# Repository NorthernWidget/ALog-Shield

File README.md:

# ALog-Shield
An Arduino shield with all the capabilities of the ALog BottleLogger

## Citation

If you use this data logger in a publication, please cite:

**Wickert, A. D., C. T. Sandell, B. Schulz, and G.-H. C. Ng (2019), [Open-source Arduino-compatible data loggers designed for field research](https://doi.org/10.5194/hess-23-2065-2019), *Hydrol. Earth Syst. Sci.*, *23*, 2065–2076, doi:10.5194/hess-23-2065-2019.**

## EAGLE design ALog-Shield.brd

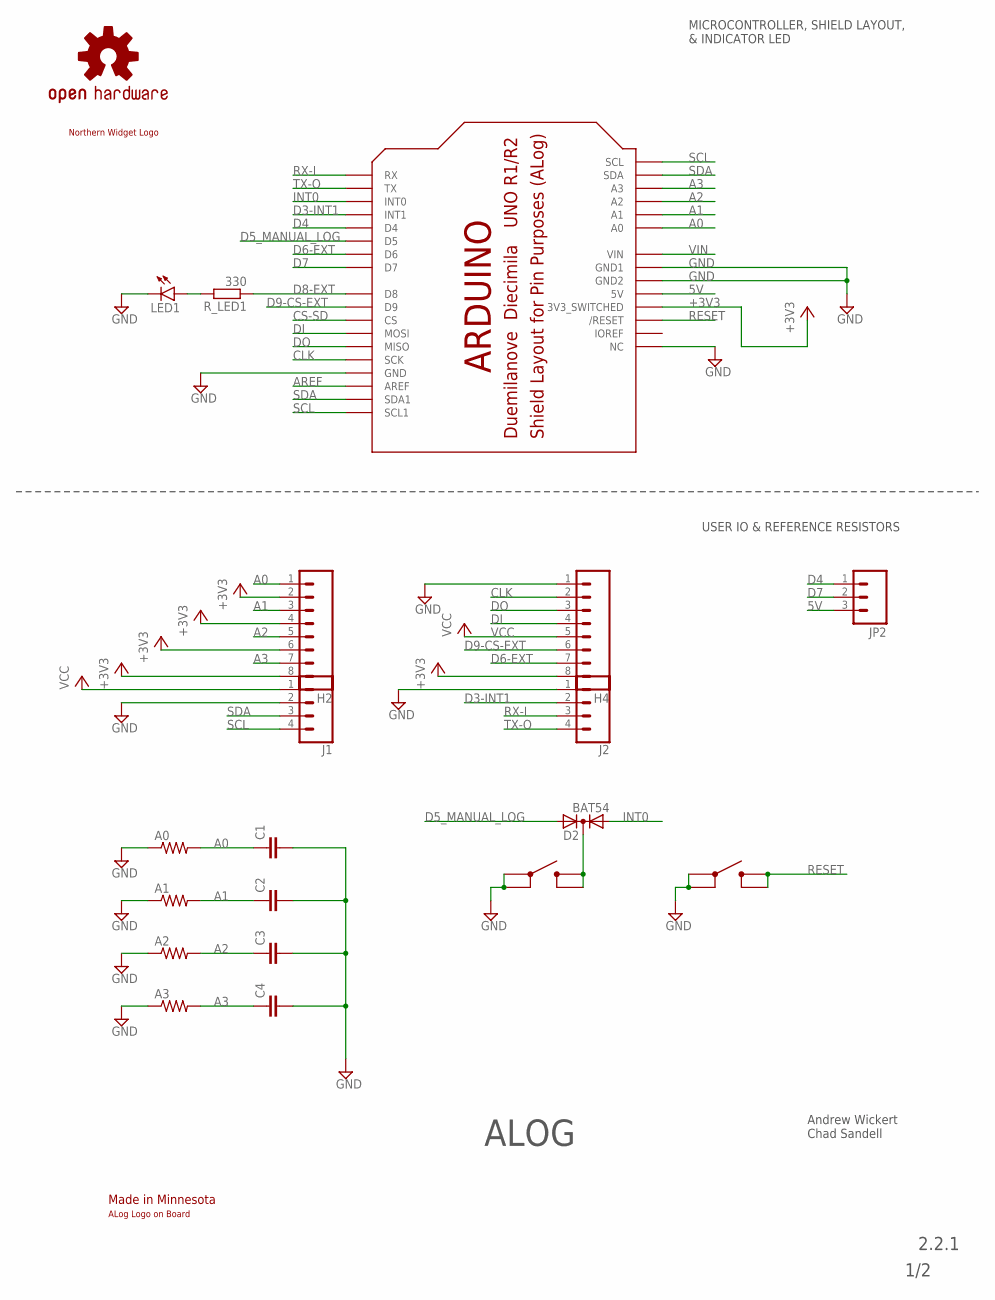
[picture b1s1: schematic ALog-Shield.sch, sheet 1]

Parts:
A0, A1, A2, A3: R-US_0207/10; 0207/10
C1, C2, C3, C4: C-EU0.1UFC0603; C0603
D2: BAT54; SOT23C
H2, H4: M083.5MM-8; SCREWTERMINAL-3.5MM-8
J1, J2: CONN_04SCREW; SCREWTERMINAL-3.5MM-4
JP2: M03SCREW; SCREWTERMINAL-3.5MM-3
LED1: LED1206; LED-1206
LOG: LOG; SWITCH_4.2X3.2
LOGO1: OSHW-LOGOL; OSHW-LOGO-L
RESET: Reset; SWITCH_4.2X3.2
R_LED1: 330; R0603
U$1: NWLOGO_MED
U$2: MADE_IN_MN_220_SHIELD; MADE_IN_MN_SHIELD_220
U$3: ALOG_LOG
U$9: AWICKERT_ARDUINO_SHIELD_PIN_PURPOSE; AWICKERT_ARDUINO_SHIELD_PINS_ONLY

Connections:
5V: JP2.3, U$9.5V
+3V3: H2.2, H2.4, H2.6, H2.8, H4.8, U$9.3.3V (3V3_SWITCHED); also elsewhere on the board
A0: A0.2, C1.1, H2.1, U$9.A0
A1: A1.2, C2.1, H2.3, U$9.A1
A2: A2.2, C3.1, H2.5, U$9.A2
A3: A3.2, C4.1, H2.7, U$9.A3
AREF: U$9.AREF; also elsewhere on the board
CLK: H4.2, U$9.D13 (SCK); also elsewhere on the board
CS-SD: U$9.D10 (CS); also elsewhere on the board
D3-INT1: J2.2, U$9.D3 (INT1)
D4: JP2.1, U$9.D4
D5_MANUAL_LOG: D2.2 (A2), U$9.D5
D6-EXT: H4.7, U$9.D6
D7: JP2.2, U$9.D7
D8-EXT: R_LED1.1, U$9.D8
D9-CS-EXT: H4.6, U$9.D9
DI: H4.4, U$9.D11 (MOSI); also elsewhere on the board
DO: H4.3, U$9.D12 (MISO); also elsewhere on the board
GND: A0.1, A1.1, A2.1, A3.1, C1.2, C2.2, C3.2, C4.2, H4.1, J1.2, J2.1, LED1.C, LOG.1, LOG.2, RESET.1, RESET.2, U$9.GND@0 (GND), U$9.GND@1 (GND1), U$9.GND@2 (GND2), U$9.NC; also elsewhere on the board
INT0: D2.1 (A1), U$9.D2 (INT0); also elsewhere on the board
LED+1: LED1.A, R_LED1.2
unnamed: D2.3 (K), LOG.3 (4), LOG.4 (3)
RESET: RESET.3 (4), RESET.4 (3), U$9.RES (/RESET)
RX-I: J2.3, U$9.RX
SCL: J1.4, U$9.A5 (SCL), U$9.SCL (SCL1); also elsewhere on the board
SDA: J1.3, U$9.A4 (SDA), U$9.SDA (SDA1); also elsewhere on the board
TX-O: J2.4, U$9.TX
VCC: H4.5, J1.1; also elsewhere on the board
VIN: U$9.VIN

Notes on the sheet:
MICROCONTROLLER, SHIELD LAYOUT, & INDICATOR LED
USER IO & REFERENCE RESISTORS
2.2.1
1/2
Andrew Wickert Chad Sandell
ALOG

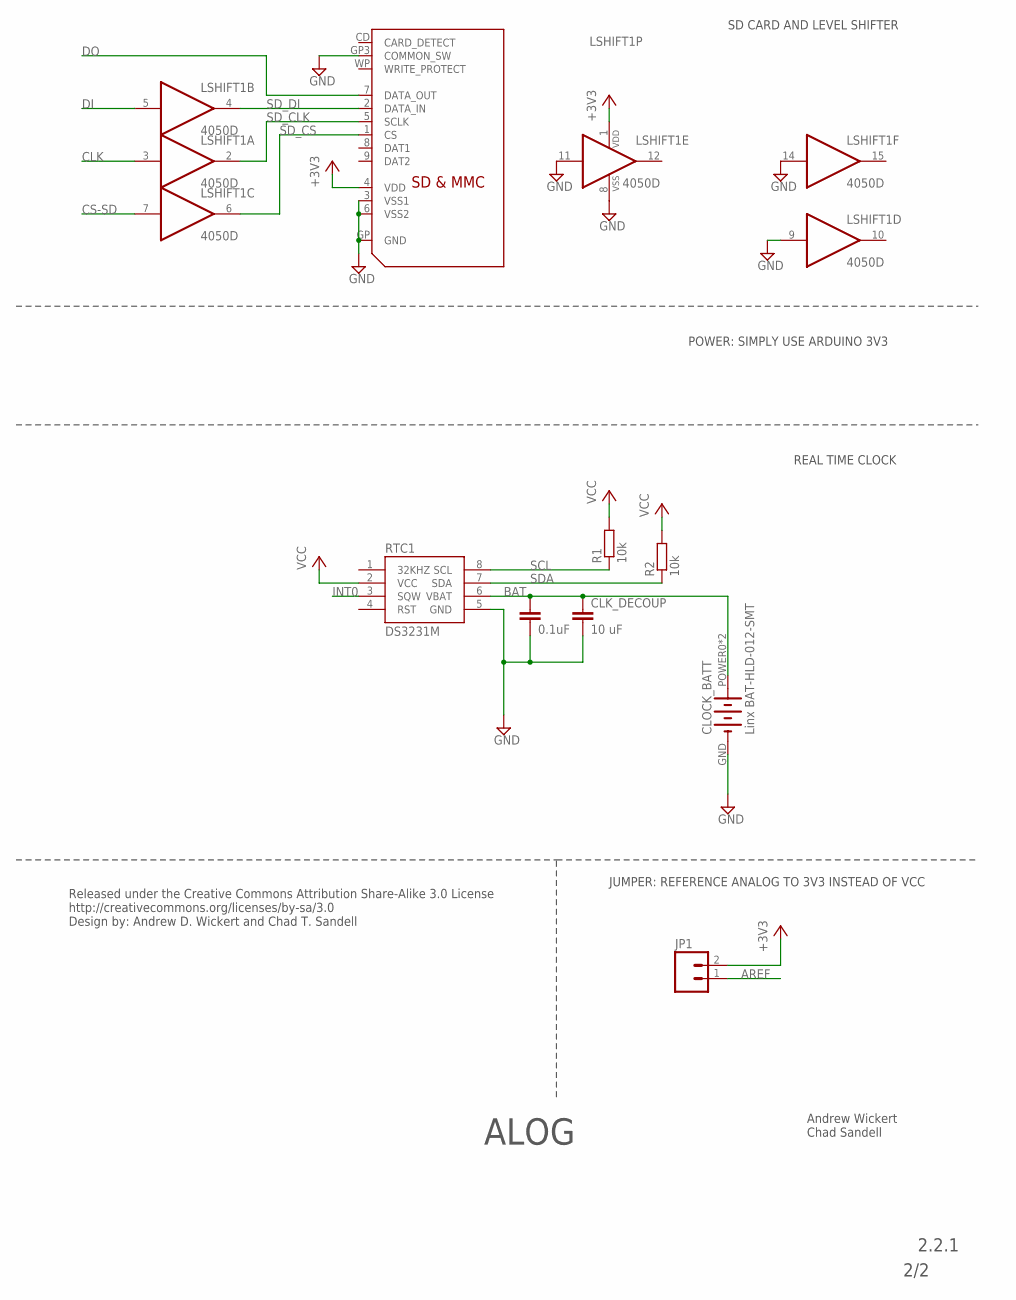
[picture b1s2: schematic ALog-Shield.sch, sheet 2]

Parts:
CLK_DECOUP: 10 uF; C0805
CLOCK_BATT: Linx BAT-HLD-012-SMT; LINX_BAT-HLD-012-SMT
CLOCK_BATT_DECOUP: 0.1uF; C0603
JP1: M02LOCK; 1X02_LOCK
LSHIFT1: 4050D; SO16
R1, R2: 10k; R0603
RTC1: DS3231M; SO08
SD1: SDMMC06132; 06132

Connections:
+3V3: JP1.2, LSHIFT1.1 (VDD), SD1.4 (VDD); also elsewhere on the board
AREF: JP1.1; also elsewhere on the board
BAT: CLK_DECOUP.1, CLOCK_BATT.POWER0 (+), CLOCK_BATT.POWER1 (+), CLOCK_BATT_DECOUP.1, RTC1.6 (VBAT)
CLK: LSHIFT1.3 (I); also elsewhere on the board
CS-SD: LSHIFT1.7 (I); also elsewhere on the board
DI: LSHIFT1.5 (I); also elsewhere on the board
DO: SD1.7 (DATA_OUT); also elsewhere on the board
GND: CLK_DECOUP.2, CLOCK_BATT.GND (-), CLOCK_BATT_DECOUP.2, LSHIFT1.8 (VSS), LSHIFT1.9 (I), LSHIFT1.11 (I), LSHIFT1.14 (I), RTC1.5 (GND), SD1.3 (VSS1), SD1.6 (VSS2), SD1.GP (GND), SD1.GP3 (COMMON_SW); also elsewhere on the board
INT0: RTC1.3 (SQW); also elsewhere on the board
SCL: R1.1, RTC1.8 (SCL); also elsewhere on the board
SDA: R2.1, RTC1.7 (SDA); also elsewhere on the board
SD_CLK: LSHIFT1.2 (O), SD1.5 (SCLK)
SD_CS: LSHIFT1.6 (O), SD1.1 (CS)
SD_DI: LSHIFT1.4 (O), SD1.2 (DATA_IN)
VCC: R1.2, R2.2, RTC1.2 (VCC); also elsewhere on the board

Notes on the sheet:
REAL TIME CLOCK
SD CARD AND LEVEL SHIFTER
POWER: SIMPLY USE ARDUINO 3V3
2.2.1
ALOG
2/2
Andrew Wickert Chad Sandell
Released under the Creative Commons Attribution Share-Alike 3.0 License http://creativecommons.org/licenses/by-sa/3.0 Design by: Andrew D. Wickert and Chad T. Sandell
JUMPER: REFERENCE ANALOG TO 3V3 INSTEAD OF VCC

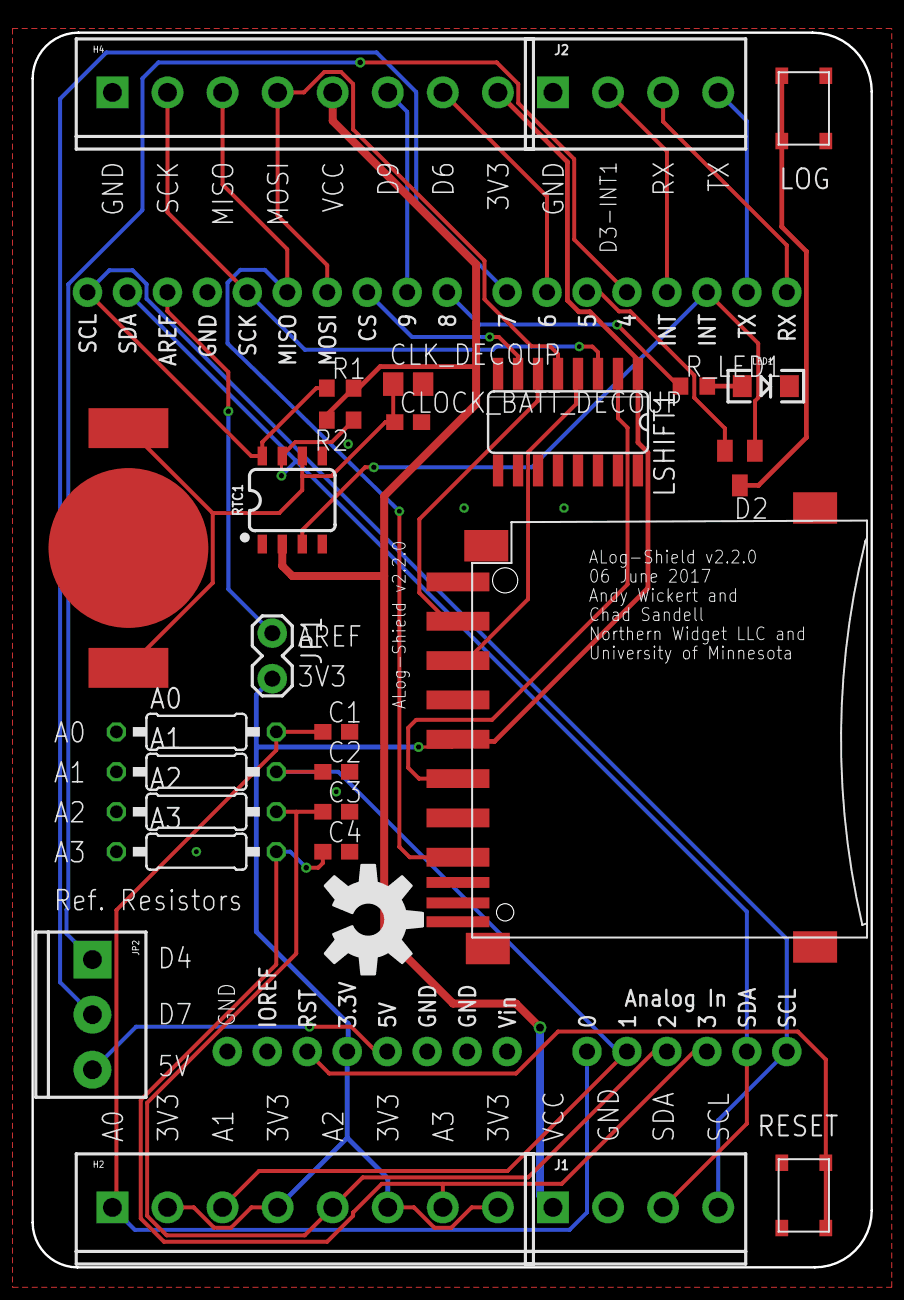
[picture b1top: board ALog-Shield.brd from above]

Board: 2 copper layers, 53.3 x 78.5 mm, 32 parts (1 on the bottom side), 32 nets.

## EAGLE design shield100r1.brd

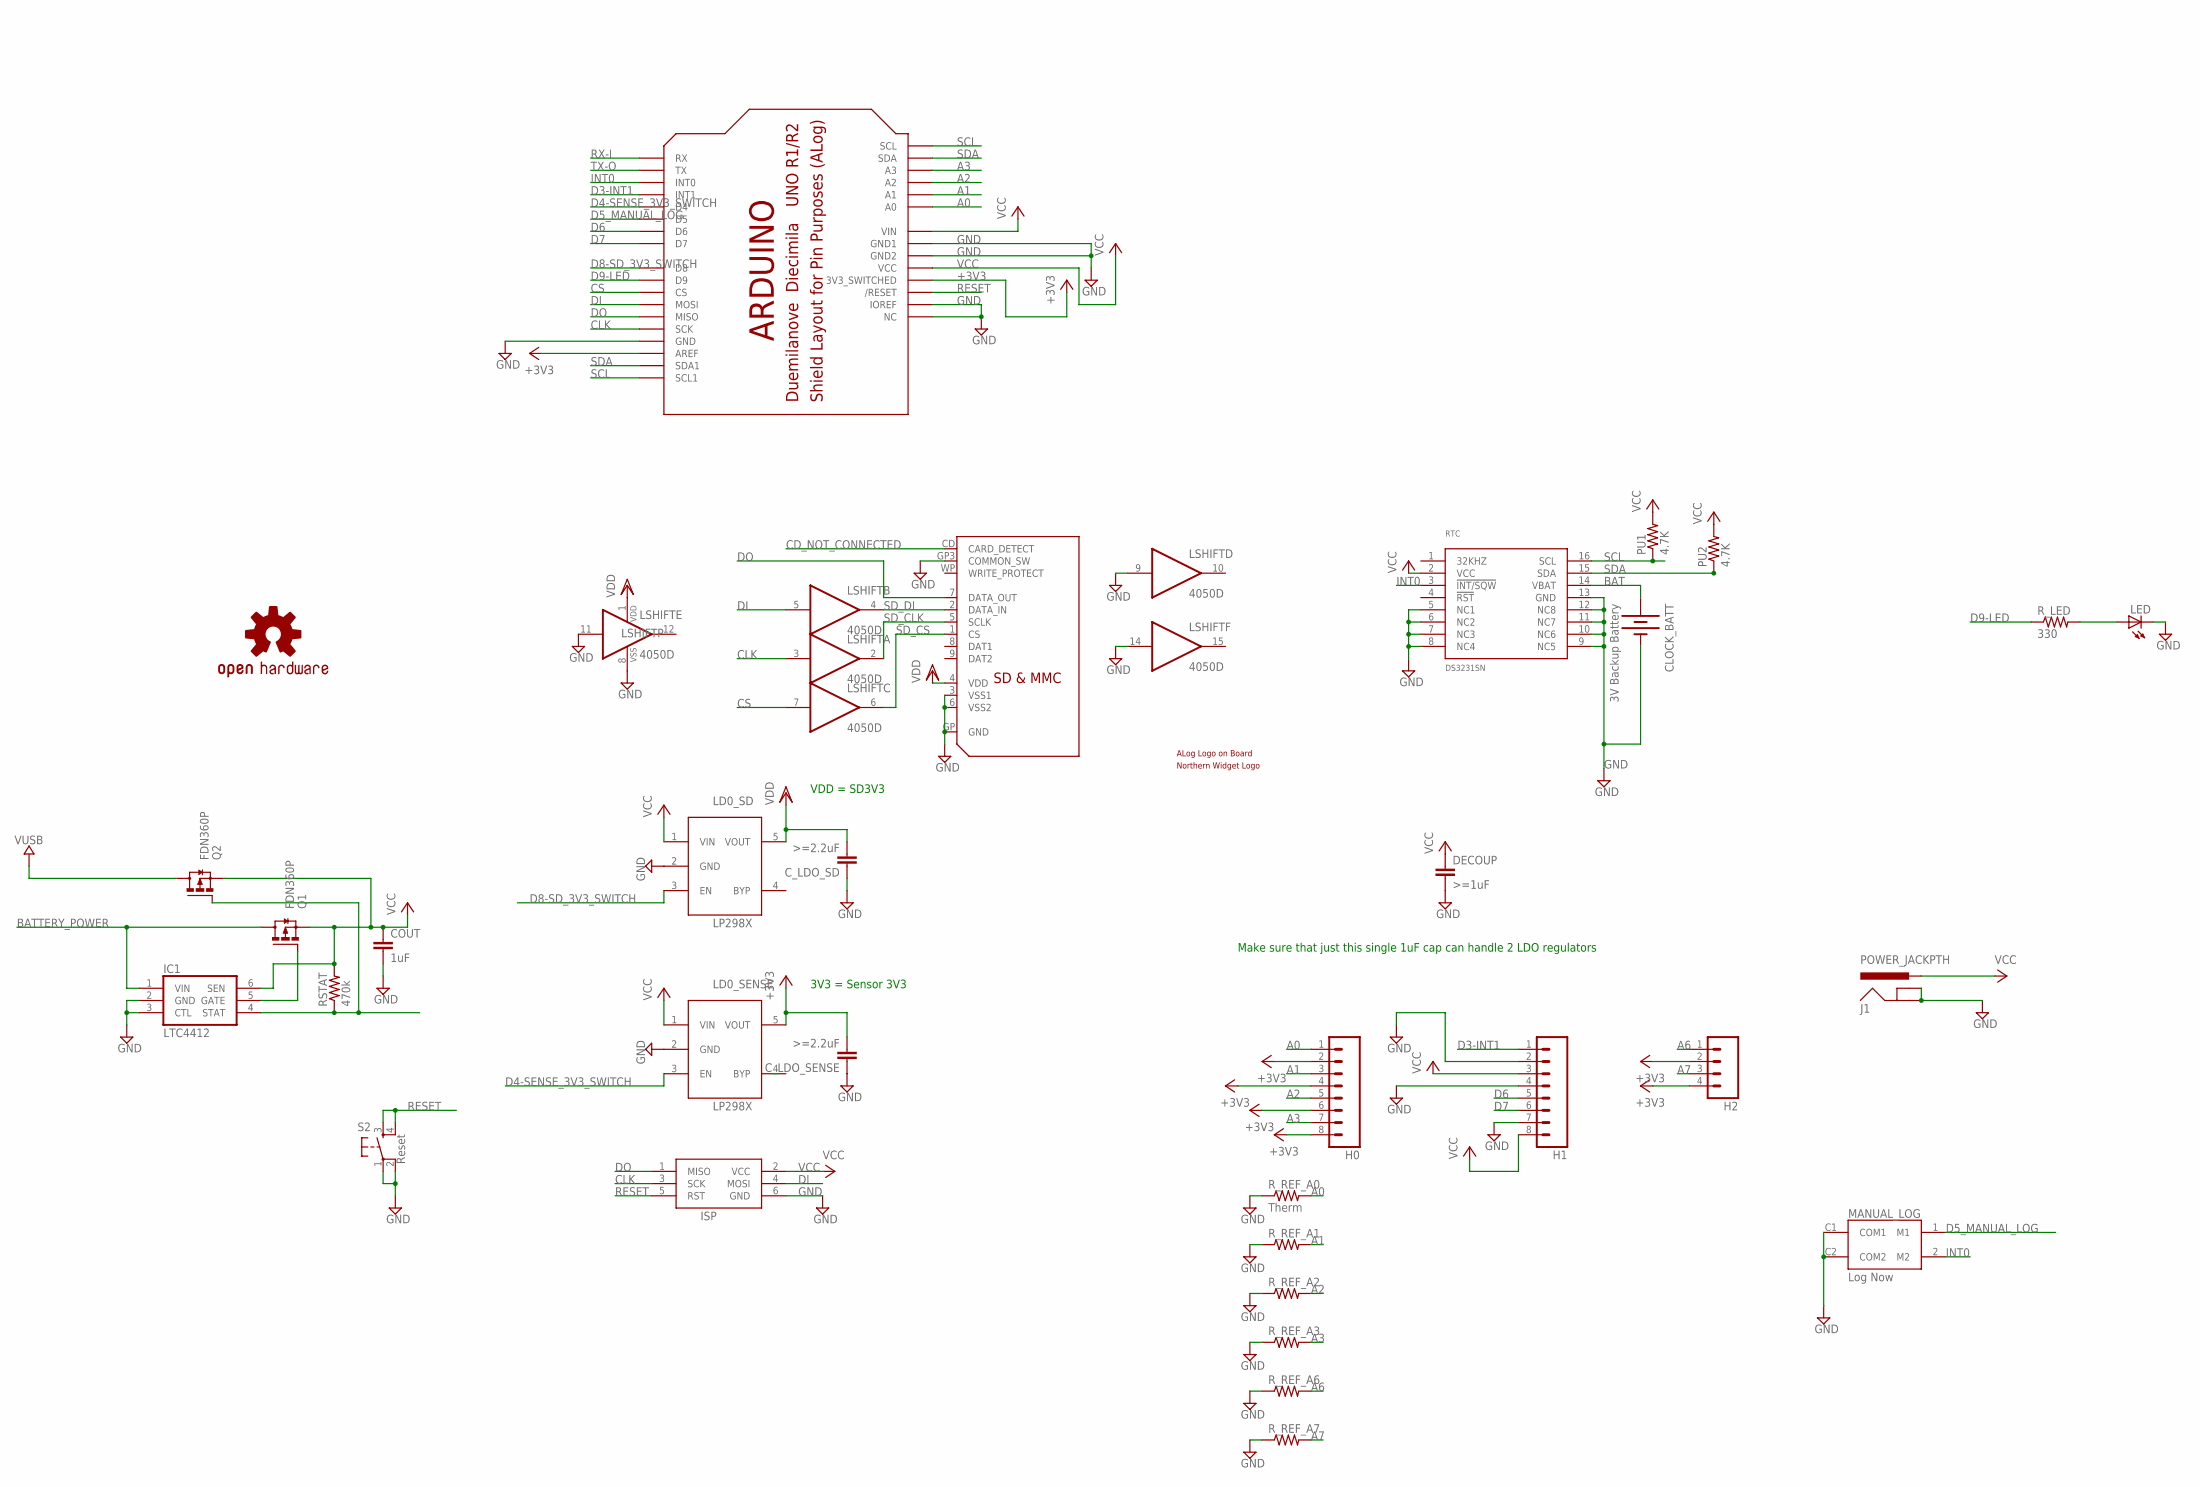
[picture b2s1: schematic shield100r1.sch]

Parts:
CLOCK_BATT: 3V Backup Battery; BATTCON_12MM_PTH
COUT: 1uF; C0603-ROUND
C_LDO_SD: >=2.2uF; C0603
C_LDO_SENSE: >=2.2uF; C0603
DECOUP: >=1uF; C0603
H0, H1: M083.5MM-8; SCREWTERMINAL-3.5MM-8
H2: M04SCREW; SCREWTERMINAL-3.5MM-4
IC1: LTC4412; TSOT23-6
ISP: AVRISP-6; AVRISP
J1: POWER_JACKPTH; POWER_JACK_PTH
LD0_SD, LD0_SENSE: LP2985; SOT23-5L
LED: LED3MM
LOGO1: OSHW-LOGOM; OSHW-LOGO-M
LSHIFT: 4050D; SO16
MANUAL_LOG: Log Now; TL_BUTTON
PU1, PU2: 4.7K; R0603
Q1, Q2: FDN360P; SUPER-SOT3
RSTAT: 470k; R0603
RTC: DS3231SN; SO16W
R_LED: 330; R0603
R_REF_A0: Therm; 0207/10
R_REF_A1, R_REF_A2, R_REF_A3, R_REF_A6, R_REF_A7: R-US_0207/10; 0207/10
S2: Reset; TACTILE_SWITCH_SMD
SD: SDMMC06132; 06132
U$2: ALOG_LOGO_V1_5.5MM; ALOG_LOGO_V1_SMALL
U$3: NWLOGO_MED
U$9: ARDUINO_SHIELD_PIN_PURPOSE; ARDUINO_SHIELD_PINS_ONLY

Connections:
+3V3: C_LDO_SENSE.2, H0.2, H0.4, H0.6, H0.8, H2.2, H2.4, LD0_SENSE.5 (VOUT), U$9.3.3V (3V3_SWITCHED), U$9.AREF
A0: H0.1, R_REF_A0.2, U$9.A0
A1: H0.3, R_REF_A1.2, U$9.A1
A2: H0.5, R_REF_A2.2, U$9.A2
A3: H0.7, R_REF_A3.2, U$9.A3
A6: H2.1, R_REF_A6.2
A7: H2.3, R_REF_A7.2
BAT: CLOCK_BATT.VCC@1 (+), RTC.14 (VBAT)
BATTERY_POWER: IC1.1 (VIN), Q1.3 (D)
CD_NOT_CONNECTED: SD.CD (CARD_DETECT)
CLK: ISP.3 (SCK), LSHIFT.3 (I), U$9.D13 (SCK)
CS: LSHIFT.7 (I), U$9.D10 (CS)
D3-INT1: H1.1, U$9.D3 (INT1)
D4-SENSE_3V3_SWITCH: LD0_SENSE.3 (EN), U$9.D4
D5_MANUAL_LOG: MANUAL_LOG.1 (M1), U$9.D5
D6: H1.5, U$9.D6
D7: H1.6, U$9.D7
D8-SD_3V3_SWITCH: LD0_SD.3 (EN), U$9.D8
D9-LED: R_LED.1, U$9.D9
DI: ISP.4 (MOSI), LSHIFT.5 (I), U$9.D11 (MOSI)
DO: ISP.1 (MISO), SD.7 (DATA_OUT), U$9.D12 (MISO)
GND: CLOCK_BATT.GND (-), COUT.2, C_LDO_SD.1, C_LDO_SENSE.1, DECOUP.2, H1.2, H1.4, H1.7, IC1.2 (GND), IC1.3 (CTL), ISP.6 (GND), J1.GND, J1.GNDBREAK, LD0_SD.2 (GND), LD0_SENSE.2 (GND), LED.K (C), LSHIFT.8 (VSS), LSHIFT.9 (I), LSHIFT.11 (I), LSHIFT.14 (I), MANUAL_LOG.C1 (COM1), MANUAL_LOG.C2 (COM2), RTC.5 (NC1), RTC.6 (NC2), RTC.7 (NC3), RTC.8 (NC4), RTC.9 (NC5), RTC.10 (NC6), RTC.11 (NC7), RTC.12 (NC8), RTC.13 (GND), R_REF_A0.1, R_REF_A1.1, R_REF_A2.1, R_REF_A3.1, R_REF_A6.1, R_REF_A7.1, S2.1, S2.2, SD.3 (VSS1), SD.6 (VSS2), SD.GP (GND), SD.GP3 (COMMON_SW), U$9.GND@0 (GND), U$9.GND@1 (GND1), U$9.GND@2 (GND2), U$9.IOREF, U$9.NC
INT0: MANUAL_LOG.2 (M2), RTC.3 (!INT/SQW), U$9.D2 (INT0)
LED+: LED.A, R_LED.2
unnamed: IC1.4 (STAT), Q2.1 (G), RSTAT.1
unnamed: IC1.5 (GATE), Q1.1 (G)
RESET: ISP.5 (RST), S2.3, S2.4, U$9.RES (/RESET)
RX-I: U$9.RX
SCL: PU1.1, RTC.16 (SCL), U$9.A5 (SCL), U$9.SCL (SCL1)
SDA: PU2.1, RTC.15 (SDA), U$9.A4 (SDA), U$9.SDA (SDA1)
SD_CLK: LSHIFT.2 (O), SD.5 (SCLK)
SD_CS: LSHIFT.6 (O), SD.1 (CS)
SD_DI: LSHIFT.4 (O), SD.2 (DATA_IN)
TX-O: U$9.TX
VCC: COUT.1, DECOUP.1, H1.3, H1.8, IC1.6 (SEN), ISP.2 (VCC), J1.PWR, LD0_SD.1 (VIN), LD0_SENSE.1 (VIN), PU1.2, PU2.2, Q1.2 (S), Q2.2 (S), RSTAT.2, RTC.2 (VCC), U$9.5V (VCC), U$9.VIN
VDD: C_LDO_SD.2, LD0_SD.5 (VOUT), LSHIFT.1 (VDD), SD.4 (VDD)
VUSB: Q2.3 (D)

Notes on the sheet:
VDD = SD3V3
3V3 = Sensor 3V3
Make sure that just this single 1uF cap can handle 2 LDO regulators

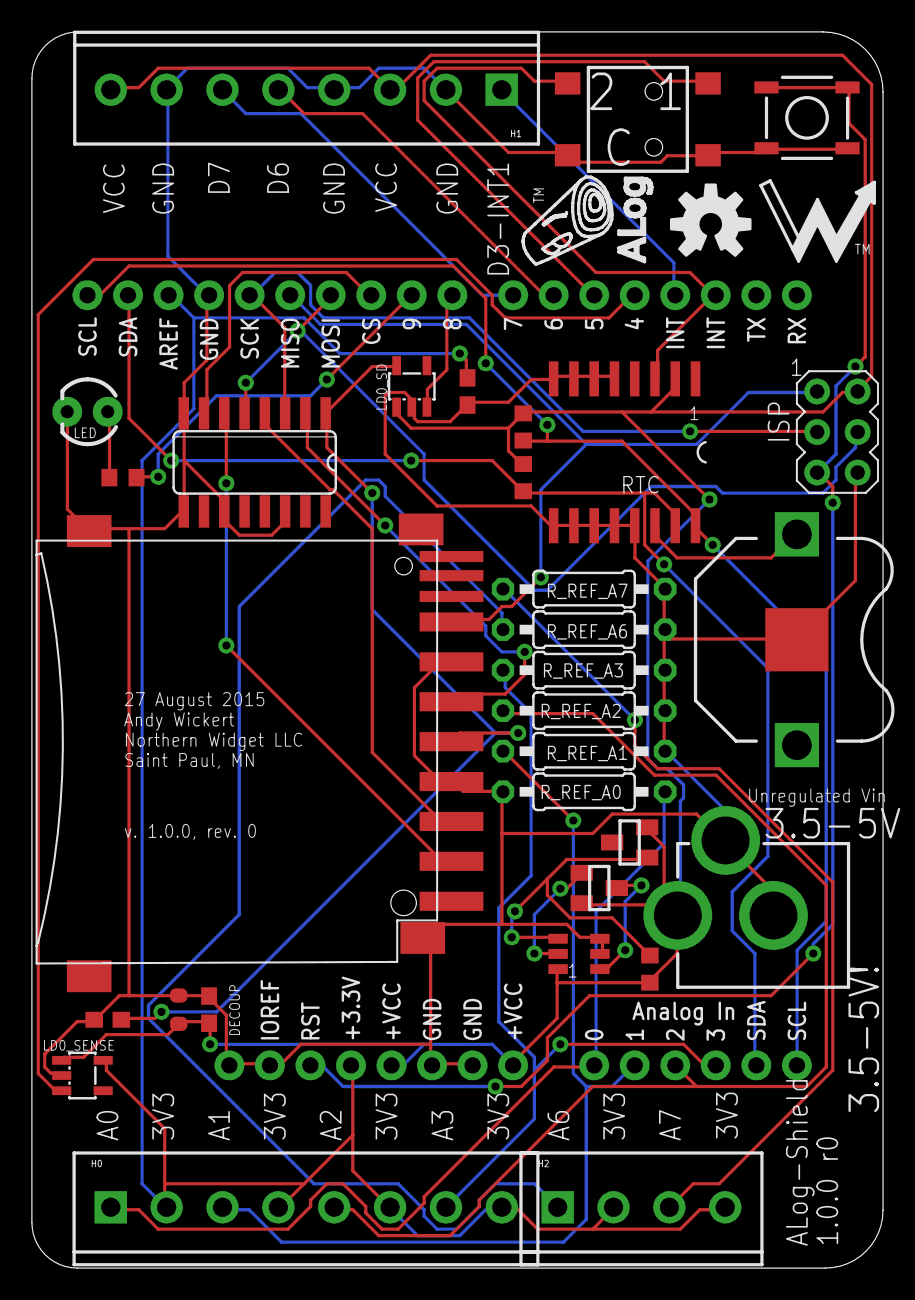
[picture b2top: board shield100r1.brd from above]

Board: 2 copper layers, 53.3 x 77.5 mm, 35 parts (0 on the bottom side), 33 nets.

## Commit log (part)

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2016-03-17 First version from August 2015
2016-03-31 messy commit of revisions with gerbers
2017-01-25 Move Gerbers, delete old version
2017-01-25 Remove derivative files
2017-01-25 Non-version-specific names: leave this for tags
2017-01-25 Transitioning to 2.0 update
2017-01-25 Semi-final parts; not placed or labeled properly
2017-03-01 Update based on new ALog BottleLogger from weeks ago; components not yet placed
2017-03-01 Components placed
2017-03-01 Connect CS and CS-SD: rename to CS-SD
2017-03-01 Board routed
2017-03-03 More space for Rref; smaller vias
2017-03-21 Remove JST power connector; move buttons to symmetrical places
2017-03-21 Use our in-stock 3.3k-ohm pull-up resistor array, even if only 2/4 in use
2017-03-21 3V3 with wide pads
2017-03-21 Long pads on cap array: easier soldering, we hope
2017-03-21 Reconnect Rref to analog pins
2017-03-21 Symmetry with screw terminals and buttons
2017-03-21 Bye bye, ISP header and reset cap and R
2017-03-21 quick update
2017-03-21 SMD battery clip
2017-03-21 changed to 12 mil vias
2017-05-02 Remove 3V3; connect 3V3 and VDD
2017-05-02 IOREF to VCC
2017-05-02 Restoring Chad's trace updates, plus my changes, plus manual reroute
2017-05-02 Implementing wiring changes; should have already uploaded?
2017-05-02 Save as and copy/paste to fix error on opening
2017-06-06 D6,D9 instead of D7,D8; SMD LED; consolodiate schematic
2017-06-06 CC-BY-SA
2017-06-06 Standardizing naming scheme
2017-06-07 Schematics and board layouts
2017-07-02 ALog and Made in MN back silk
2017-07-02 Update silk and OSE logo
2017-07-14 Added D4 and D7 out put points, will not populate with screw terminals
2017-11-08 Fix zip file version name
2017-11-09 changes made to allow OSH Park board run
2017-12-31 screw terminal + spacing to text
2018-01-02 3V3 (not VDD) and VCC
2018-01-07 Beta for review
2018-02-03 1206-->0805 10uF, rm floating vias
2018-02-03 AREF to 3V3 jumper
2018-02-03 New buttons: consistent with TLog
2018-02-07 New button routed
2018-02-07 DRC: routing
2018-02-07 3.3K RTC PU array to discrete (10K?)
2018-02-07 rm cap array
2018-02-08 Bobby's caps
2018-02-08 R220K to R330K ColdSilicon
2018-02-08 ColdSilicon DS3231M
2018-02-08 re-route with ColdSilicon
2018-02-08 R330ohms
2018-02-08 07 Feb design
2018-02-08 IO Ref conversion
2018-02-09 PU, reroute, 5V terminal
2018-02-09 Larger via
2018-02-12 Added final Gerbers for Mrk 2.2.1
    Cleaned up routing, fixed button issue, generated gerbers for Mrk 2.2.1
2018-02-23 ColdSilicon parts update; abbrev. silk
2018-06-17 Create LICENSE
2018-09-15 Cleaned up scheamtic, fixed IOREF issue, added PDF, v2.2.1
    Should generate gerbers for v2.2.1 before adding tag, simply disconnected IOREF from Vcc, in future could add voltage shifting based on IOREF as well
2018-09-15 annotations; v2.2.0 Sorry Bobby -- I now realize that the last release was the 2.2.0 beta, so we did not have to increment to 2.2.1! Rebuilt the PDFs, but not the combined one (removed the old one)
2019-01-13 bom for DigiKey
2019-01-13 rmv tmp files

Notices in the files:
parts and their libraries:
SparkFun-Aesthetics: Licensing: CC v3.0 Share-Alike You are welcome to use this library for commercial purposes.
SparkFun-Connectors: Licensing: Creative Commons ShareAlike 4.0 International - https://creativecommons.org/licenses/by-sa/4.0
